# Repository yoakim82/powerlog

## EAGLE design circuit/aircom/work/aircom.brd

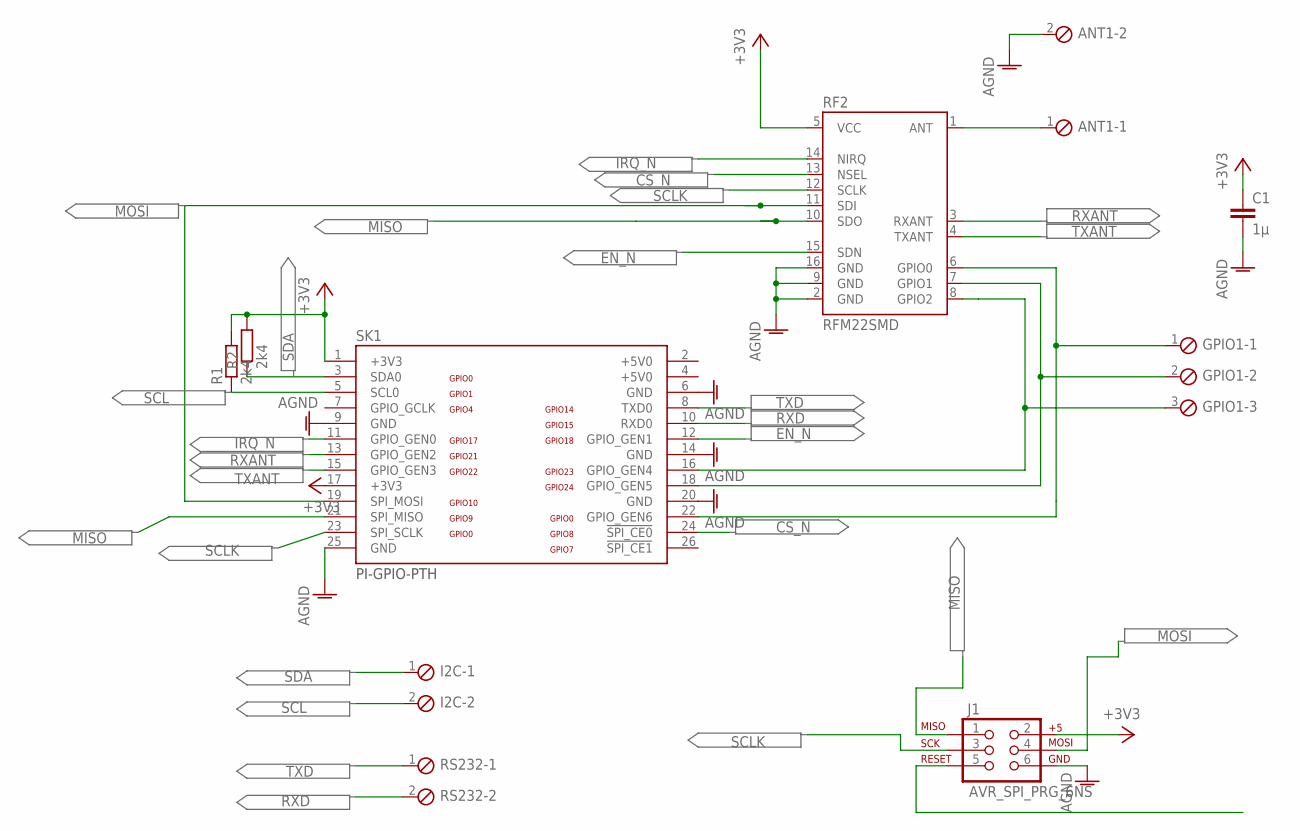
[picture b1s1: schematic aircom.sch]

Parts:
ANT1: MPT2; 2POL254
C1: 1µ; C0805
GPIO1: MPT3; 3POL254
I2C: MPT2; 2POL254
J1: AVR_SPI_PRG_6NS; 2X3-NS
R1, R2: 2k4; R0603
RF2: RFM22SMD; RFM22-XXX-S2
RS232: MPT2; 2POL254
SK1: PI-GPIO-PTH; GPIO-CONNECTOR

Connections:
+3V3: C1.1, J1.2, R1.2, R2.2, RF2.5 (VCC), SK1.1 (+3V3), SK1.17 (+3V3)
+5V0: SK1.2 (+5V0), SK1.4 (+5V0)
AGND: ANT1.2, C1.2, J1.6, RF2.2 (GND), RF2.9 (GND), RF2.16 (GND), SK1.6 (GND), SK1.9 (GND), SK1.14 (GND), SK1.20 (GND), SK1.25 (GND)
ANT: ANT1.1, RF2.1 (ANT)
CS_N: RF2.13 (NSEL), SK1.24 (!SPI_CE0)
EN_N: RF2.15 (SDN), SK1.12 (GPIO_GEN1)
GPIO0: GPIO1.1, RF2.6 (GPIO0), SK1.22 (GPIO_GEN6)
GPIO1: GPIO1.2, RF2.7 (GPIO1), SK1.18 (GPIO_GEN5)
GPIO2: GPIO1.3, RF2.8 (GPIO2), SK1.16 (GPIO_GEN4)
IRQ_N: RF2.14 (NIRQ), SK1.11 (GPIO_GEN0)
MISO: J1.1, RF2.10 (SDO), SK1.21 (SPI_MISO)
MOSI: J1.4, RF2.11 (SDI), SK1.19 (SPI_MOSI)
RESET1: J1.5
RXANT: RF2.3 (RXANT), SK1.13 (GPIO_GEN2)
RXD: RS232.2, SK1.10 (RXD0)
SCL: I2C.2, R1.1, SK1.5 (SCL0)
SCLK: J1.3, RF2.12 (SCLK), SK1.23 (SPI_SCLK)
SDA: I2C.1, R2.1, SK1.3 (SDA0)
TXANT: RF2.4 (TXANT), SK1.15 (GPIO_GEN3)
TXD: RS232.1, SK1.8 (TXD0)

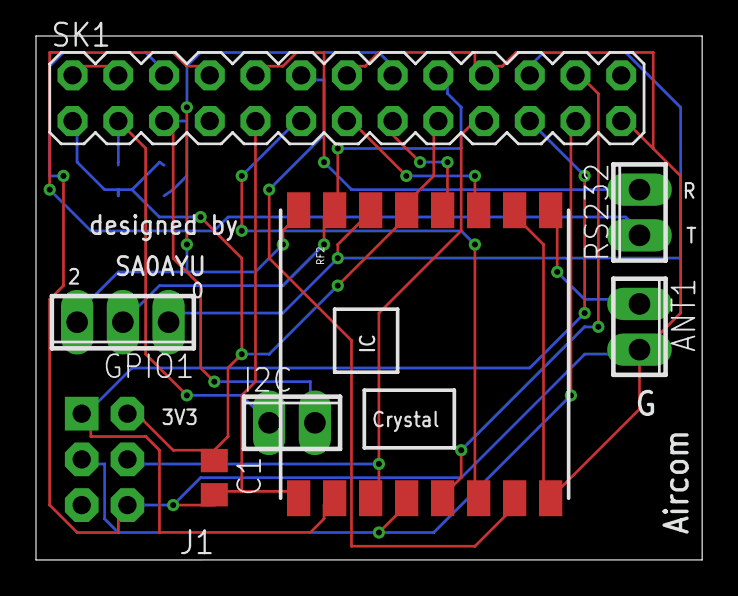
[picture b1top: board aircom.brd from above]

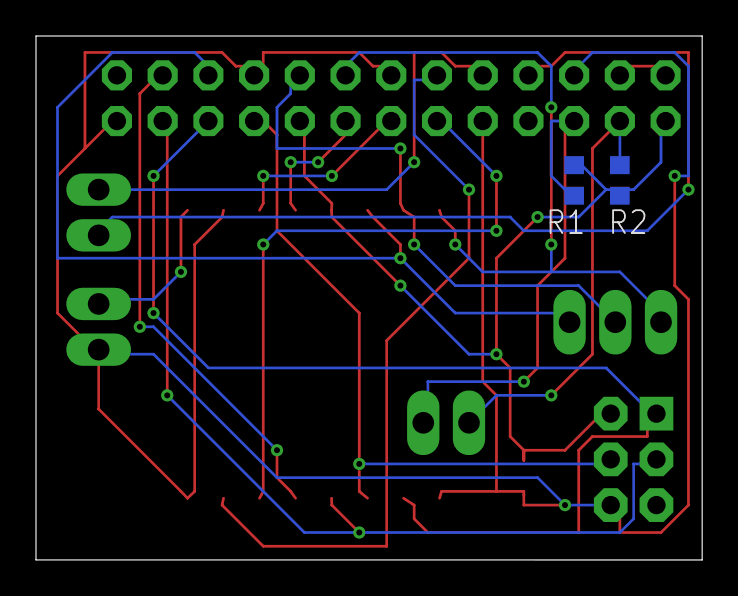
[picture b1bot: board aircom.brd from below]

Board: 2 copper layers, 37.0 x 29.1 mm, 10 parts (2 on the bottom side), 19 nets.

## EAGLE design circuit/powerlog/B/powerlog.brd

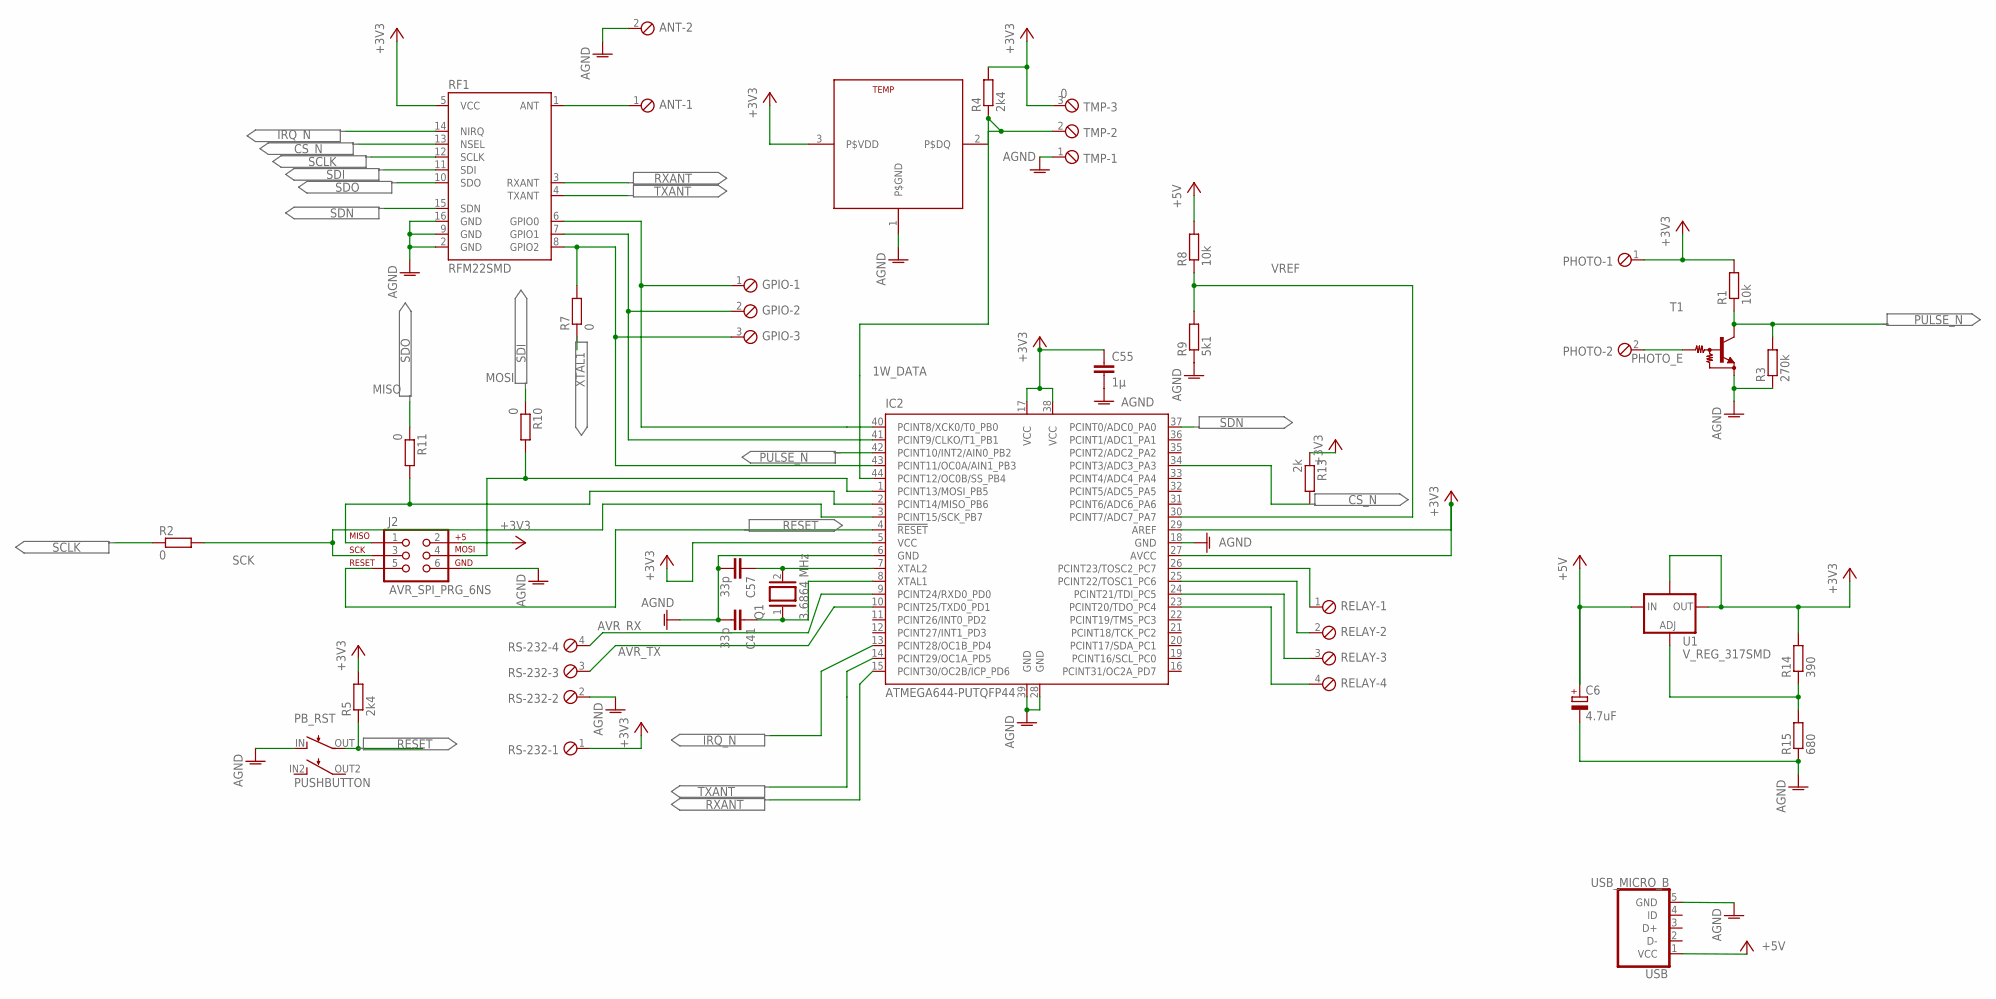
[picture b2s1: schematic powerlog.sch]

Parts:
ANT: MPT2; 2POL254
C6: 4.7uF; SMC_CAP_B
C41, C57: 33p; C0603
C55: 1µ; C0805
GPIO: MPT3; 3POL254
IC2: ATMEGA644-PUTQFP44; TQFP44
J2: AVR_SPI_PRG_6NS; 2X3-NS
PB_RST: PUSHBUTTON
PHOTO: MPT2; 2POL254
Q1: 3.6864 MHz; Q
R1, R8: 10k; R0603
R2, R7, R10, R11: 0; R0603
R3: 270k; R0603
R4, R5: 2k4; R0603
R9: 5k1; R0603
R13: 2k; R0603
R14: 390; R0603
R15: 680; R0603
RELAY: MPT4; 4POL254
RF1: RFM22SMD; RFM22-XXX-S2
RS-232: MPT4; 4POL254
T1: NPN-DRIVER; SC59_EBC
TEMP: DS18S20T; TO92-
TMP: 0; 3POL254
U1: V_REG_317SMD; SOT223
USB: USB_MICRO_B

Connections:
1W_DATA: IC2.44 (PCINT12/OC0B/SS_PB4), R4.1, TEMP.2 (P$DQ), TMP.2
+3V3: C55.1, IC2.5 (VCC), IC2.17 (VCC), IC2.27 (AVCC), IC2.29 (AREF), IC2.38 (VCC), J2.2, PHOTO.1, R1.2, R4.2, R5.2, R13.1, R14.2, RF1.5 (VCC), RS-232.1, TEMP.3 (P$VDD), TMP.3, U1.2 (OUT), U1.4 (OUT_TOP)
+5V: C6.+, R8.2, U1.3 (IN), USB.1 (VCC)
AGND: ANT.2, C6.-, C41.2, C55.2, C57.2, IC2.6 (GND), IC2.18 (GND), IC2.28 (GND), IC2.39 (GND), J2.6, PB_RST.IN, R3.1, R9.1, R15.1, RF1.2 (GND), RF1.9 (GND), RF1.16 (GND), RS-232.2, T1.E, TEMP.1 (P$GND), TMP.1, USB.5 (GND)
AVR_RX: IC2.9 (PCINT24/RXD0_PD0), RS-232.4
AVR_TX: IC2.10 (PCINT25/TXD0_PD1), RS-232.3
CS_N: IC2.34 (PCINT3/ADC3_PA3), R13.2, RF1.13 (NSEL)
GPIO0: GPIO.1, IC2.40 (PCINT8/XCK0/T0_PB0), RF1.6 (GPIO0)
GPIO1: GPIO.2, IC2.41 (PCINT9/CLKO/T1_PB1), RF1.7 (GPIO1)
GPIO2: GPIO.3, IC2.43 (PCINT11/OC0A/AIN1_PB3), R7.2, RF1.8 (GPIO2)
IRQ_N: IC2.13 (PCINT28/OC1B_PD4), RF1.14 (NIRQ)
MISO: IC2.2 (PCINT14/MISO_PB6), J2.1, R11.2
MOSI: IC2.1 (PCINT13/MOSI_PB5), J2.4, R10.2
unnamed: ANT.1, RF1.1 (ANT)
unnamed: IC2.26 (PCINT23/TOSC2_PC7), RELAY.1
unnamed: IC2.25 (PCINT22/TOSC1_PC6), RELAY.2
unnamed: IC2.24 (PCINT21/TDI_PC5), RELAY.3
unnamed: IC2.23 (PCINT20/TDO_PC4), RELAY.4
unnamed: R14.1, R15.2, U1.1 (ADJ)
PHOTO_E: PHOTO.2, T1.B
PULSE_N: IC2.42 (PCINT10/INT2/AIN0_PB2), R1.1, R3.2, T1.C
RESET: IC2.4 (!RESET), J2.5, PB_RST.OUT, R5.1
RXANT: IC2.15 (PCINT30/OC2B/ICP_PD6), RF1.3 (RXANT)
SCK: IC2.3 (PCINT15/SCK_PB7), J2.3, R2.2
SCLK: R2.1, RF1.12 (SCLK)
SDI: R10.1, RF1.11 (SDI)
SDN: IC2.37 (PCINT0/ADC0_PA0), RF1.15 (SDN)
SDO: R11.1, RF1.10 (SDO)
TXANT: IC2.14 (PCINT29/OC1A_PD5), RF1.4 (TXANT)
VREF: IC2.30 (PCINT7/ADC7_PA7), R8.1, R9.2
XTAL1: C41.1, IC2.8 (XTAL1), Q1.1, R7.1
XTAL2: C57.1, IC2.7 (XTAL2), Q1.2

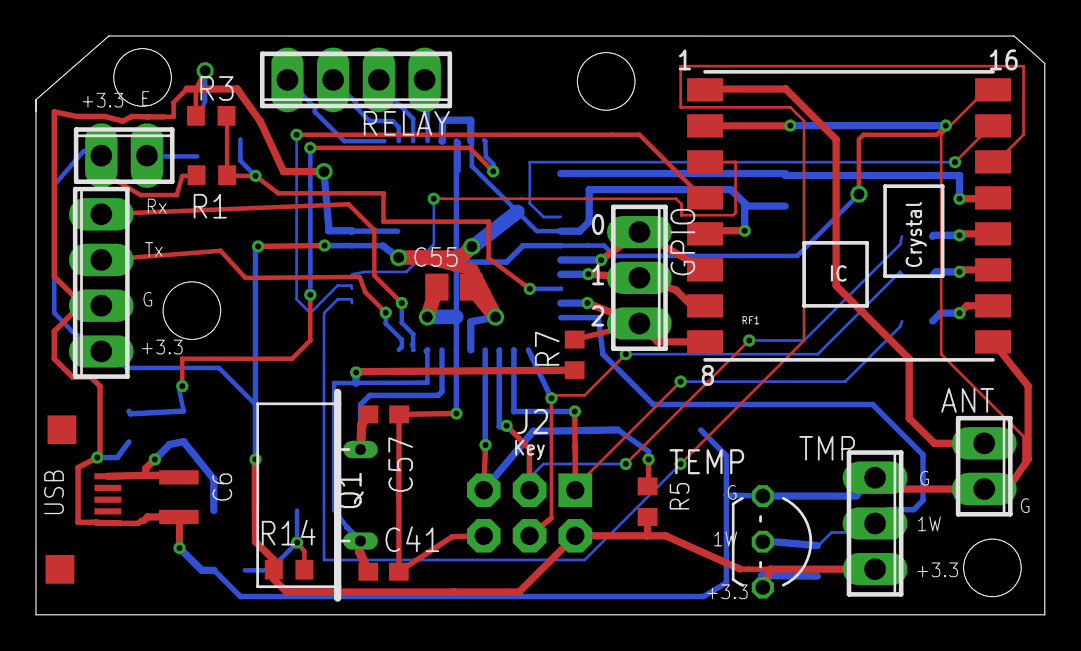
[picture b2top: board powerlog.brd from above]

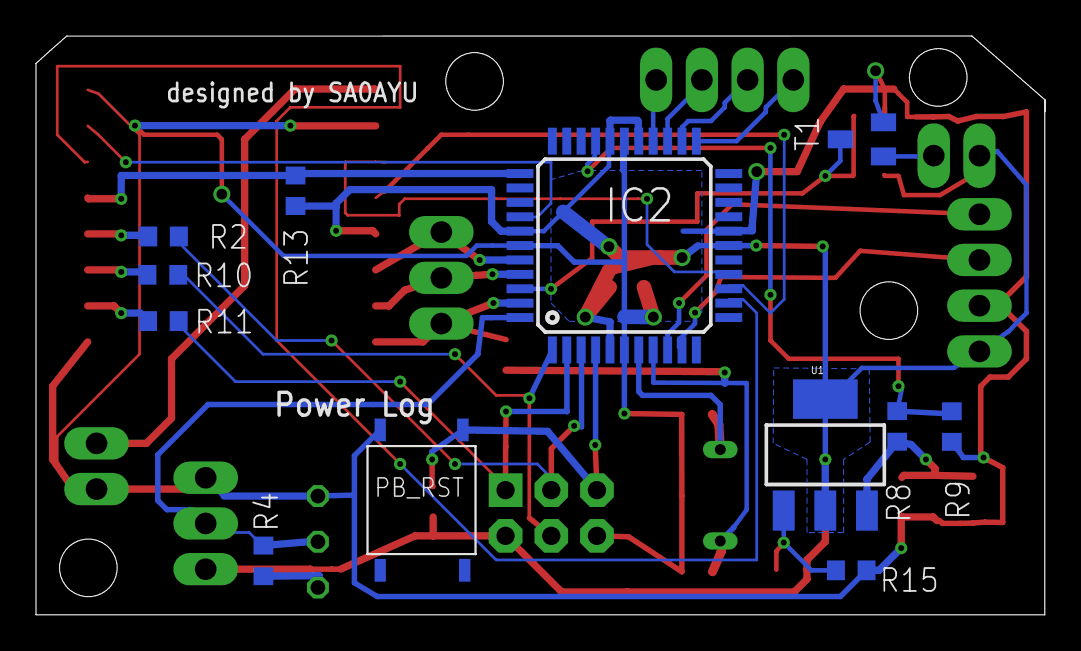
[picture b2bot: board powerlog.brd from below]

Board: 2 copper layers, 56.0 x 32.2 mm, 32 parts (12 on the bottom side), 32 nets.

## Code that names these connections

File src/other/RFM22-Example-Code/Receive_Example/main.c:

/*
    Created on: Mar. 30, 2010
	Under project: RFM22
	Author: Jim Lindblom
	RFM22 Receive Example
	
	Hardware: Arduino Pro (ATmega328) running at 8Mhz, 3.3V
	Wiring:
	RFM22 BOB	|	Arduino Pro
	----------------------------
		GND		|	GND
		3.3V	|	3.3V
		GPIO0	|	NC
		GPIO1	|	NC
		GPIO2	|	NC
		RXANT	|	PD6 (D6)
		TXANT	|	PD5 (D5)
		IRQ		|	PD4 (D4)
		CSN		|	PB0 (D8)
		SCK		|	PB4 (D13)
		SDI		|	PB2 (D11)
		SDO		|	PB3 (D12)
		
	Antenna is a 17cm piece of wire sticking straight up into the air.
*/

//======================//
//======================//
#include <avr/io.h>
#include <stdio.h>
#include "RFM22.h"
//======================//
//======================//

#define sbi(var, mask)   ((var) |= (uint8_t)(1 << mask))
#define cbi(var, mask)   ((var) &= (uint8_t)~(1 << mask))

//======================//
//Arduino Pro Specific Defines
#define LED 5

//RFM22 Defines
#define CS 7 //pin for chip select
#define CSPORT PORTD
#define TXANT 5	// PD5
#define RXANT 6	// PD6
#define NIRQ 4	// PD4

//======================//
//======================//

void ioinit(void);
void delay_ms(uint16_t x);
void delay_us(uint16_t x);

//======================//
//======================//

static int uart_putchar(char c, FILE *stream);
uint8_t uart_getchar(void);
static FILE mystdout = FDEV_SETUP_STREAM(uart_putchar, NULL, _FDEV_SETUP_WRITE);

//======================//
//======================//

void init_SPI(void);
void init_RFM22(void);
void to_rx_mode(void);
void rx_reset(void);
void checkINT(void);
void txdata(char data);
char rxdata(void);
char read(uint8_t address);
void write(uint8_t address, char data);

//======================//
//Global Variables
unsigned char RF_RXBUF[35];

int main(void)
{
	unsigned char i, chksum;

	ioinit();
	init_SPI();
	sbi(CSPORT,CS);
	printf("********RFM22 Communication Test********\n");

	//====================//
	//Communications Test
	printf("Reading DTYPE register, should be 0x08: %d", read(DTYPE));
	
	printf("\n*****************************************\n\n");
	
	init_RFM22();	// Initialize all RFM22 registers
	printf("Entering RX Mode...\n");
	to_rx_mode();
	
	while(1)
	{
		if((PIND & (1<<NIRQ)) == 0)	//Interrupt will be generated if data is recieved
		{
			// Read 18-byte packet into RF_RXBUF[]:
			for(i=0; i<17; i++)
			{
				RF_RXBUF[i] = read(0x7F);
			}
			
			// Check that the checksum matches up:
			chksum = 0;
			for(i=0; i<16; i++)
				chksum += RF_RXBUF[i];
		
			// If checksum is good, print out what was received into the terminal
			if(chksum == RF_RXBUF[16])
			{
				write(0x07, 0x01);	// To ready mode
				printf("Received: ");
				for(i=0; i<17; i++)
					printf("%c", RF_RXBUF[i]);	// Print characters if passed the checksum
				printf("\n");
				//printf("To Ready mode\n");
			}
			// otherwise reset and start listening again
			else
			{
				rx_reset();
				//printf("Bad checksum RX RESET...Listening again\n");
			}
			delay_ms(50);
		}
	}
}

// Initialize the RFM22 for transmitting
void init_RFM22(void)
{
	write(INTEN2, 0x00);	// Disable all interrupts
	write(OMFC1, 0x01);		// Set READY mode
	write(0x09, 0x7F);		// Cap = 12.5pF
	//write(0x0A, 0x05);		// Clk output is 2MHz
	
	write(0x0B, 0xF4);		// GPIO0 is for RX data output
	write(0x0C, 0xEF);		// GPIO1 is TX/RX data CLK output
	write(0x0D, 0x00);		// GPIO2 for MCLK output
	write(0x0E, 0x00);		// GPIO port use default value
	
	write(0x0F, 0x70);		// NO ADC used
	write(0x10, 0x00);		// no ADC used
	write(0x12, 0x00);		// No temp sensor used
	write(0x13, 0x00);		// no temp sensor used
	
	write(0x70, 0x20);		// No manchester code, no data whiting, data rate < 30Kbps
	
	write(0x1C, 0x1D);		// IF filter bandwidth
	write(0x1D, 0x40);		// AFC Loop
	//write(0x1E, 0x0A);	// AFC timing
	
	write(0x20, 0xA1);		// clock recovery
	write(0x21, 0x20);		// clock recovery
	write(0x22, 0x4E);		// clock recovery
	write(0x23, 0xA5);		// clock recovery
	write(0x24, 0x00);		// clock recovery timing
	write(0x25, 0x0A);		// clock recovery timing
	
	//write(0x2A, 0x18);
	write(0x2C, 0x00);
	write(0x2D, 0x00);
	write(0x2E, 0x00);
	
	write(0x6E, 0x27);		// TX data rate 1
	write(0x6F, 0x52);		// TX data rate 0
	
	write(0x30, 0x8C);		// Data access control
	
	write(0x32, 0xFF);		// Header control
	
	write(0x33, 0x42);		// Header 3, 2, 1, 0 used for head length, fixed packet length, synchronize word length 3, 2,
	
	write(0x34, 64);		// 64 nibble = 32 byte preamble
	write(0x35, 0x20);		// 0x35 need to detect 20bit preamble
	write(0x36, 0x2D);		// synchronize word
	write(0x37, 0xD4);
	write(0x38, 0x00);
	write(0x39, 0x00);
	write(0x3A, 's');		// set tx header 3
	write(0x3B, 'o');		// set tx header 2
	write(0x3C, 'n');		// set tx header 1
	write(0x3D, 'g');		// set tx header 0
	write(0x3E, 17);		// set packet length to 17 bytes
	
	write(0x3F, 's');		// set rx header
	write(0x40, 'o');
	write(0x41, 'n');
	write(0x42, 'g');
	write(0x43, 0xFF);		// check all bits
	write(0x44, 0xFF);		// Check all bits
	write(0x45, 0xFF);		// check all bits
	write(0x46, 0xFF);		// Check all bits
	
	write(0x56, 0x01);
	
	write(0x6D, 0x07);		// Tx power to max
	
	write(0x79, 0x00);		// no frequency hopping
	write(0x7A, 0x00);		// no frequency hopping
	
	write(0x71, 0x22);		// GFSK, fd[8]=0, no invert for TX/RX data, FIFO mode, txclk-->gpio
	
	write(0x72, 0x48);		// Frequency deviation setting to 45K=72*625
	
	write(0x73, 0x00);		// No frequency offset
	write(0x74, 0x00);		// No frequency offset
	
	write(0x75, 0x53);		// frequency set to 434MHz
	write(0x76, 0x64);		// frequency set to 434MHz
	write(0x77, 0x00);		// frequency set to 434Mhz
	
	write(0x5A, 0x7F);
	write(0x59, 0x40);
	write(0x58, 0x80);
	
	write(0x6A, 0x0B);
	write(0x68, 0x04);
	write(0x1F, 0x03);
}

void to_rx_mode(void)
{
	write(0x07, 0x01);	// to ready mode
	
	sbi(PORTD, RXANT);
	cbi(PORTD, TXANT);
	delay_ms(50);
	rx_reset();
}

void rx_reset(void)
{
	unsigned char i;
	
	write(0x07, 0x01);	// to ready mode
	
	i = read(0x03);
	i = read(0x04);
	
	write(0x7E, 17);
	
	write(0x08, 0x03);
	write(0x08, 0x00);
	
	write(0x07, 5);
	
	write(0x05, 2);
}

void checkINT(void)
{
	if ((PIND & (1<<NIRQ)) == 0)
		printf("INT == 0\n");
	else
		printf("INT == 1\n");
}

void write(uint8_t address, char data)
{
	//write any data byte to any single address
	//adds a 0 to the MSB of the address byte (WRITE mode)
	
	address |= 0x80;

	cbi(CSPORT,CS);
	delay_ms(1);
	txdata(address);
	delay_ms(1);
	txdata(data);
	delay_ms(1);
	sbi(CSPORT,CS);
}

char read(uint8_t address)
{
	//returns the contents of any 1 byte register from any address
	//sets the MSB for every address byte (READ mode)

	char byte;

	address &= 0x7F;

	cbi(CSPORT,CS);
	txdata(address);
	byte = rxdata();
	sbi(CSPORT,CS);

	return byte;
}

char rxdata(void)
{
	SPDR = 0x55;
	while((SPSR&0x80) == 0x00);

	return SPDR;
}

void txdata(char data)
{
	SPDR = data;
	while((SPSR&0x80) == 0x00);
}

void init_SPI(void)
{
	// enable SPI
	// make SPI master
	// SCLK idle low
	// sample data on rising edge
	// SPCR |= 0b01010011;	// SPIclk = FOSC/128
	SPCR |= 0b01010000;	// SPIclk = Fosc/4
}

static int uart_putchar(char c, FILE *stream)
{
    if (c == '\n') uart_putchar('\r', stream);

    loop_until_bit_is_set(UCSR1A, UDRE1);
    UDR1 = c;

    return 0;
}

uint8_t uart_getchar(void)
{
    while( !(UCSR1A & (1<<RXC1)) );
    return(UDR1);
}


void ioinit (void)
{
    //1 = output, 0 = input
    DDRB = 0b10111000; //MISO input, pb2:0 input (GPIO)
    DDRC = 0b11111111; //All outputs
    DDRD = 0b11101010; //PORTD (RX on PD0), PD4 input (IRQ)
	stdout = &mystdout; //Required for printf init
	int MYUBRR = 12;
	UBRR1H = (MYUBRR) >> 8;
	UBRR1L = MYUBRR;
	UCSR1B = (1<<RXEN1)|(1<<TXEN1);
	UCSR1C = (3<<UCSZ10);
	UCSR1A = (1<<U2X1);

	
	TCCR2B = (1<<CS21);
	
	cbi(PORTD, TXANT);
	cbi(PORTD, RXANT);
}

//General short delays
void delay_ms(uint16_t x)
{
    for (; x > 0 ; x--)
        delay_us(1000);
}

//General short delays
void delay_us(uint16_t x)
{
    while(x > 256)
    {
        TIFR2 = (1<<TOV2); //Clear any interrupt flags on Timer2
        TCNT2 = 0; //256 - 125 = 131 : Preload timer 2 for x clicks. Should be 1us per click
        while( (TIFR2 & (1<<TOV2)) == 0);

        x -= 256;
    }

    TIFR2 = (1<<TOV2); //Clear any interrupt flags on Timer2
    TCNT2= 256 - x; //256 - 125 = 131 : Preload timer 2 for x clicks. Should be 1us per click
    while( (TIFR2 & (1<<TOV2)) == 0);
}

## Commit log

2015-10-07 test
